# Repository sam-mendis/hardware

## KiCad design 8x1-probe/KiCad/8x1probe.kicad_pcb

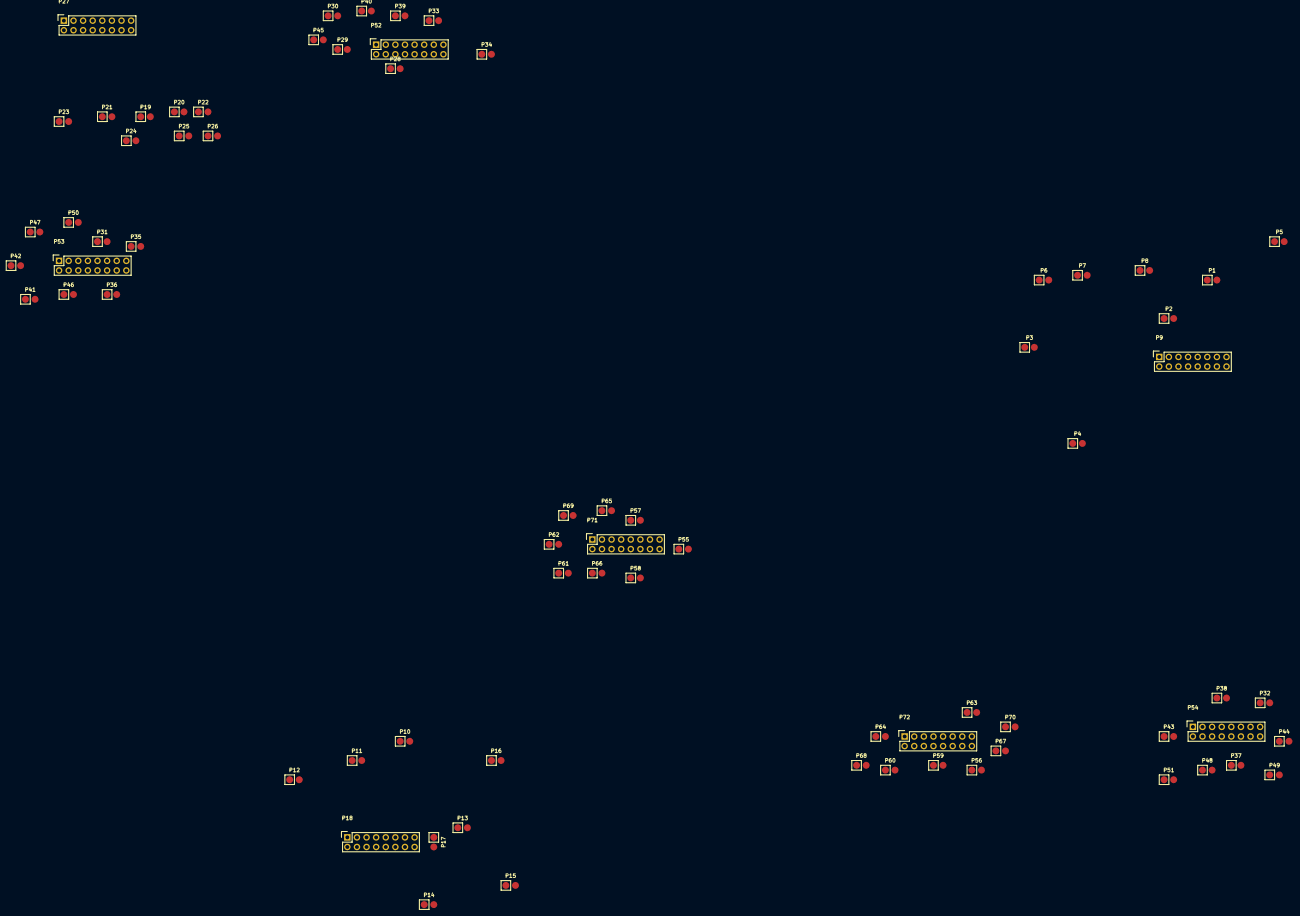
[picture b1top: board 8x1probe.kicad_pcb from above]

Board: 2 copper layers, 72 parts (0 on the bottom side), 128 nets, no tracks yet.

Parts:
P1, P2, P3, P4, P5, P6, P7, P8, P10, P11, P12, P13, P14, P15, P16, P17, P19, P20, P21, P22, P23, P24, P25, P26, P28, P29, P30, P31, P32, P33, P34, P35, P36, P37, P38, P39, P40, P41, P42, P43, P44, P45, P46, P47, P48, P49, P50, P51, P55, P56, P57, P58, P59, P60, P61, P62, P63, P64, P65, P66, P67, P68, P69, P70: 2x1_pogo_pin
P9, P18, P27, P52, P53, P54, P71, P72: CONN_02X08; Socket_Strip_Straight_2x08

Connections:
/CONN-A1: P8.1, P9.1
/CONN-A2: P8.2, P9.2
/CONN-A3: P7.1, P9.3
/CONN-A4: P7.2, P9.4
/CONN-A5: P6.1, P9.5
/CONN-A6: P6.2, P9.6
/CONN-A7: P4.1, P9.7
/CONN-A8: P4.2, P9.8
/CONN-A9: P5.1, P9.9
/CONN-A10: P5.2, P9.10
/CONN-A11: P2.1, P9.11
/CONN-A12: P2.2, P9.12
/CONN-A13: P3.1, P9.13
/CONN-A14: P3.2, P9.14
/CONN-A15: P1.1, P9.15
/CONN-A16: P1.2, P9.16
/CONN-B1: P17.1, P18.1
/CONN-B2: P17.2, P18.2
/CONN-B3: P16.1, P18.3
/CONN-B4: P16.2, P18.4
/CONN-B5: P15.1, P18.5
/CONN-B6: P15.2, P18.6
/CONN-B7: P13.1, P18.7
/CONN-B8: P13.2, P18.8
/CONN-B9: P14.1, P18.9
/CONN-B10: P14.2, P18.10
/CONN-B11: P11.1, P18.11
/CONN-B12: P11.2, P18.12
/CONN-B13: P12.1, P18.13
/CONN-B14: P12.2, P18.14
/CONN-B15: P10.1, P18.15
/CONN-B16: P10.2, P18.16
/CONN-C1: P26.1, P27.1
/CONN-C2: P26.2, P27.2
/CONN-C3: P25.1, P27.3
/CONN-C4: P25.2, P27.4
/CONN-C5: P24.1, P27.5
/CONN-C6: P24.2, P27.6
/CONN-C7: P22.1, P27.7
/CONN-C8: P22.2, P27.8
/CONN-C9: P23.1, P27.9
/CONN-C10: P23.2, P27.10
/CONN-C11: P20.1, P27.11
/CONN-C12: P20.2, P27.12
/CONN-C13: P21.1, P27.13
/CONN-C14: P21.2, P27.14
/CONN-C15: P19.1, P27.15
/CONN-C16: P19.2, P27.16
/CONN-D1: P50.1, P53.1
/CONN-D2: P50.2, P53.2
/CONN-D3: P47.1, P53.3
/CONN-D4: P47.2, P53.4
/CONN-D5: P46.1, P53.5
/CONN-D6: P46.2, P53.6
/CONN-D7: P41.1, P53.7
/CONN-D8: P41.2, P53.8
/CONN-D9: P42.1, P53.9
/CONN-D10: P42.2, P53.10
/CONN-D11: P35.1, P53.11
/CONN-D12: P35.2, P53.12
/CONN-D13: P36.1, P53.13
/CONN-D14: P36.2, P53.14
/CONN-D15: P31.1, P53.15
/CONN-D16: P31.2, P53.16
/CONN-E1: P51.1, P54.1
/CONN-E2: P51.2, P54.2
/CONN-E3: P49.1, P54.3
/CONN-E4: P49.2, P54.4
/CONN-E5: P48.1, P54.5
/CONN-E6: P48.2, P54.6
/CONN-E7: P43.1, P54.7
/CONN-E8: P43.2, P54.8
/CONN-E9: P44.1, P54.9
/CONN-E10: P44.2, P54.10
/CONN-E11: P37.1, P54.11
/CONN-E12: P37.2, P54.12
/CONN-E13: P38.1, P54.13
/CONN-E14: P38.2, P54.14
/CONN-E15: P32.1, P54.15
/CONN-E16: P32.2, P54.16
/CONN-F1: P45.1, P52.1
/CONN-F2: P45.2, P52.2
/CONN-F3: P40.1, P52.3
/CONN-F4: P40.2, P52.4
/CONN-F5: P39.1, P52.5
/CONN-F6: P39.2, P52.6
/CONN-F7: P33.1, P52.7
/CONN-F8: P33.2, P52.8
/CONN-F9: P34.1, P52.9
/CONN-F10: P34.2, P52.10
/CONN-F11: P29.1, P52.11
/CONN-F12: P29.2, P52.12
/CONN-F13: P30.1, P52.13
/CONN-F14: P30.2, P52.14
/CONN-F15: P28.1, P52.15
/CONN-F16: P28.2, P52.16
/CONN-G1: P69.1, P71.1
/CONN-G2: P69.2, P71.2
/CONN-G3: P66.1, P71.3
/CONN-G4: P66.2, P71.4
/CONN-G5: P65.1, P71.5
/CONN-G6: P65.2, P71.6
/CONN-G7: P61.1, P71.7
/CONN-G8: P61.2, P71.8
/CONN-G9: P62.1, P71.9
/CONN-G10: P62.2, P71.10
/CONN-G11: P57.1, P71.11
/CONN-G12: P57.2, P71.12
/CONN-G13: P58.1, P71.13
/CONN-G14: P58.2, P71.14
/CONN-G15: P55.1, P71.15
/CONN-G16: P55.2, P71.16
/CONN-H1: P70.1, P72.1
/CONN-H2: P70.2, P72.2
/CONN-H3: P68.1, P72.3
/CONN-H4: P68.2, P72.4
/CONN-H5: P67.1, P72.5
/CONN-H6: P67.2, P72.6
/CONN-H7: P63.1, P72.7
/CONN-H8: P63.2, P72.8
/CONN-H9: P64.1, P72.9
/CONN-H10: P64.2, P72.10
/CONN-H11: P59.1, P72.11
/CONN-H12: P59.2, P72.12
/CONN-H13: P60.1, P72.13
/CONN-H14: P60.2, P72.14
/CONN-H15: P56.1, P72.15
/CONN-H16: P56.2, P72.16

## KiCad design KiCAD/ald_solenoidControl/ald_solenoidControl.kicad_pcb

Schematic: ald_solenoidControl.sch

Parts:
C1: 0.1uF; C_0603_HandSoldering
J1, J4: Conn_01x14; Pin_Header_Straight_1x14_Pitch2.54mm
J2, J3: Conn_02x06_Odd_Even; Socket_Strip_Straight_2x06_Pitch2.54mm
JP1, JP6: Jumper_NC_Small; GS2
JP2, JP3, JP4, JP5: Jumper_NC_Dual; GS3
L1: GREY@CHRISTOFORO.NET; logo
R1: R; R_1206
R2: 500K; R_0805_HandSoldering
RN1, RN2, RN3, RN4: R_Pack04; DIP-8_SMD
U1, U2, U3, U4, U5, U6, U7, U8, U9, U10, U11, U12, U13, U14, U15, U16, U17, U18, U19, U20, U21: ASSR-1611; DIP-6_W7.62mm
U22: MCP23S17; DIP-28_W7.62mm

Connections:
+3V3: J1.2, J4.2
+5V: C1.1, J1.1, J4.1, JP2.1, JP3.1, JP4.1, JP5.1, U21.6, U22.9, U22.18
/BOT: U10.1, U20.1, U22.22
/I1: J3.2, U12.6
/I2: J2.1, U13.6
/I3: J3.6, U14.6
/I4: J2.5, U15.6
/I5: J3.10, U16.6
/I6: J2.9, U17.6
/I7: J3.11, U18.6
/I8: J2.12, U19.6
/IB: J3.7, U20.6
/IT: J2.8, U11.6
/P1: U2.1, U12.1, U22.1
/P2: U3.1, U13.1, U22.2
/P3: U4.1, U14.1, U22.3
/P4: U5.1, U15.1, U22.4
/P5: U6.1, U16.1, U22.5
/P6: U7.1, U17.1, U22.6
/P7: U8.1, U18.1, U22.7
/P8: U9.1, U19.1, U22.8
/PRE_GND: R1.2, U1.2, U2.2, U3.2, U4.2, U5.2, U6.2, U7.2, U8.2, U9.2, U10.2, U11.2, U12.2, U13.2, U14.2, U15.2, U16.2, U17.2, U18.2, U19.2, U20.2, U21.2
/TOP: U1.1, U11.1, U22.21
/V1: J3.4, U2.6
/V2: J2.3, U3.6
/V3: J3.8, U4.6
/V4: J2.7, U5.6
/V5: J3.12, U6.6
/V6: J2.11, U7.6
/V7: J3.9, U8.6
/V8: J2.10, U9.6
/VB: J3.5, U10.6
/VT: J2.6, U1.6
/V_D_EN: U21.1, U22.23
A0: JP2.2, U22.15
A1: JP3.2, U22.16
A2: JP4.2, U22.17
GND: C1.2, J1.10, J2.4, J3.1, J3.3, J4.10, JP2.3, JP3.3, JP4.3, JP5.3, R1.1, U22.10
I+: J1.11, J4.11, U12.4, U13.4, U14.4, U15.4, U16.4, U17.4, U18.4, U19.4
I-: J1.14, J4.14, U11.4, U20.4
MISO: J1.7, J4.7, U22.14
MOSI: J1.8, J4.8, U22.13
unnamed: J1.6, JP1.2
unnamed: J4.6, JP6.1
unnamed: R2.1, U21.5
SCK: J1.9, J4.9, U22.12
SCL: J1.5, J4.5
SDA: J1.4, J4.4
V+: J1.12, J4.12, U2.4, U3.4, U4.4, U5.4, U6.4, U7.4, U8.4, U9.4
V-: J1.13, J4.13, U1.4, U10.4
V_D: J1.3, J2.2, J4.3, R2.2
~CS: JP1.1, JP5.2, JP6.2, U22.11

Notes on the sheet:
ADDRESS SELECTION
POWER FLAGS
BOARD TYPE DETECTION
CONNECTORS TO SPRING PIN BOARD
RIGHT SIDE BUS CONNECTIONS
LEFT SIDE BUS CONNECTIONS

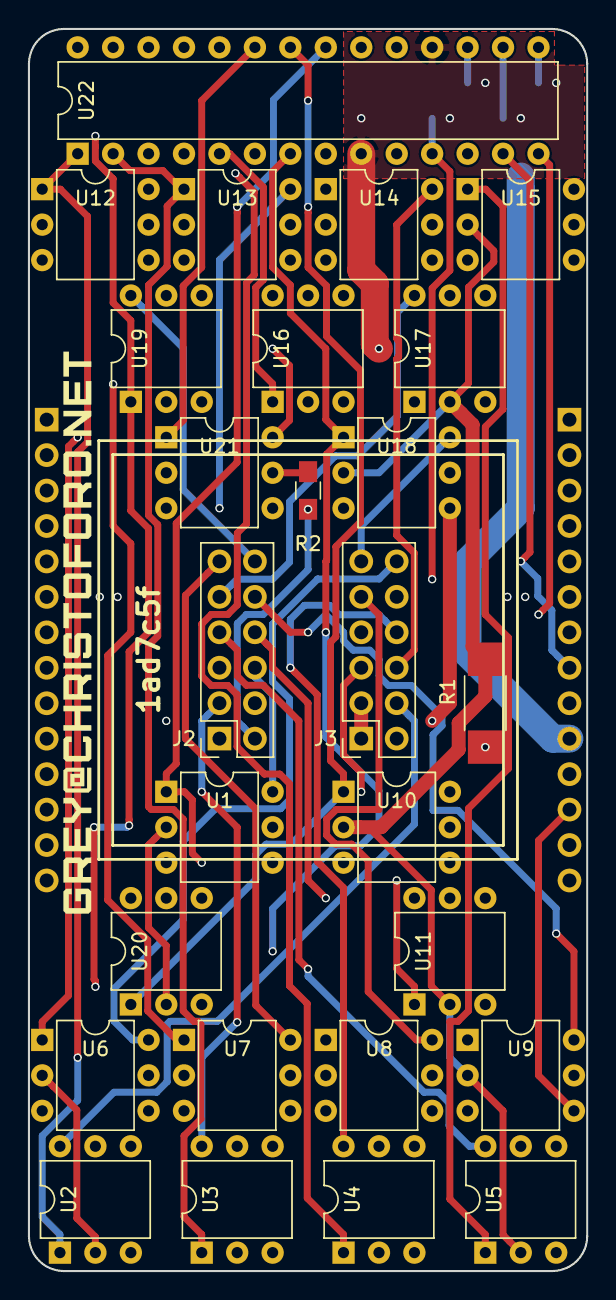
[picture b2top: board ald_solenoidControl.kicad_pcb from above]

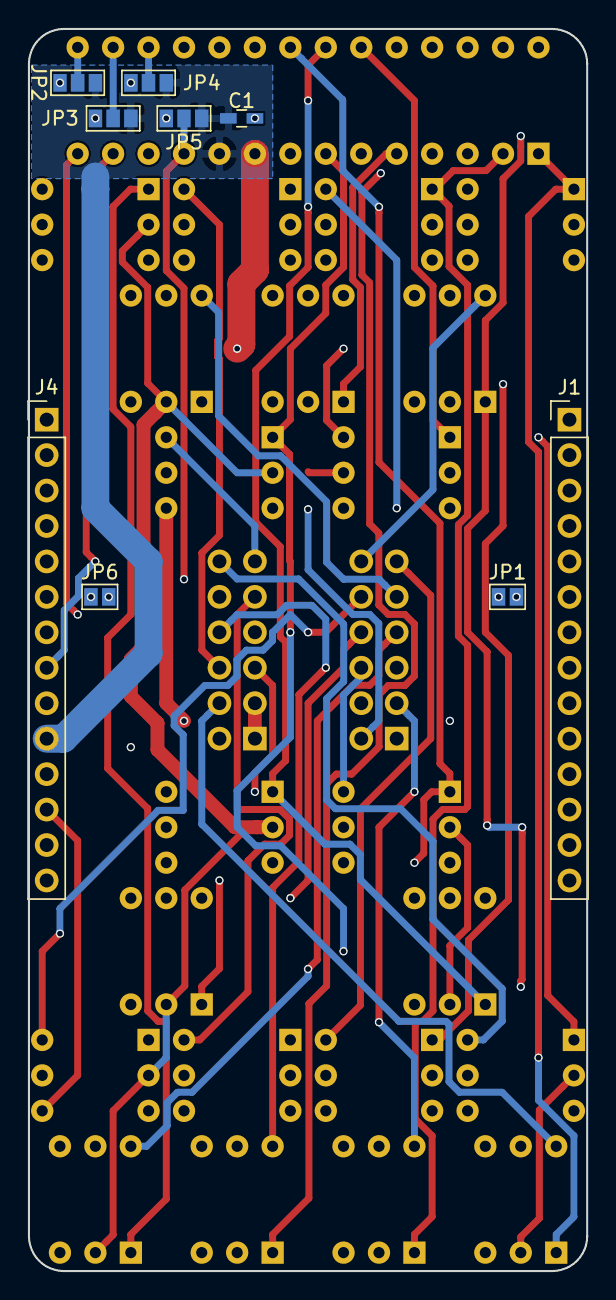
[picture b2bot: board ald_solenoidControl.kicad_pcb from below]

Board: 4 copper layers, 40.0 x 89.0 mm, 36 parts (9 on the bottom side), 52 nets.

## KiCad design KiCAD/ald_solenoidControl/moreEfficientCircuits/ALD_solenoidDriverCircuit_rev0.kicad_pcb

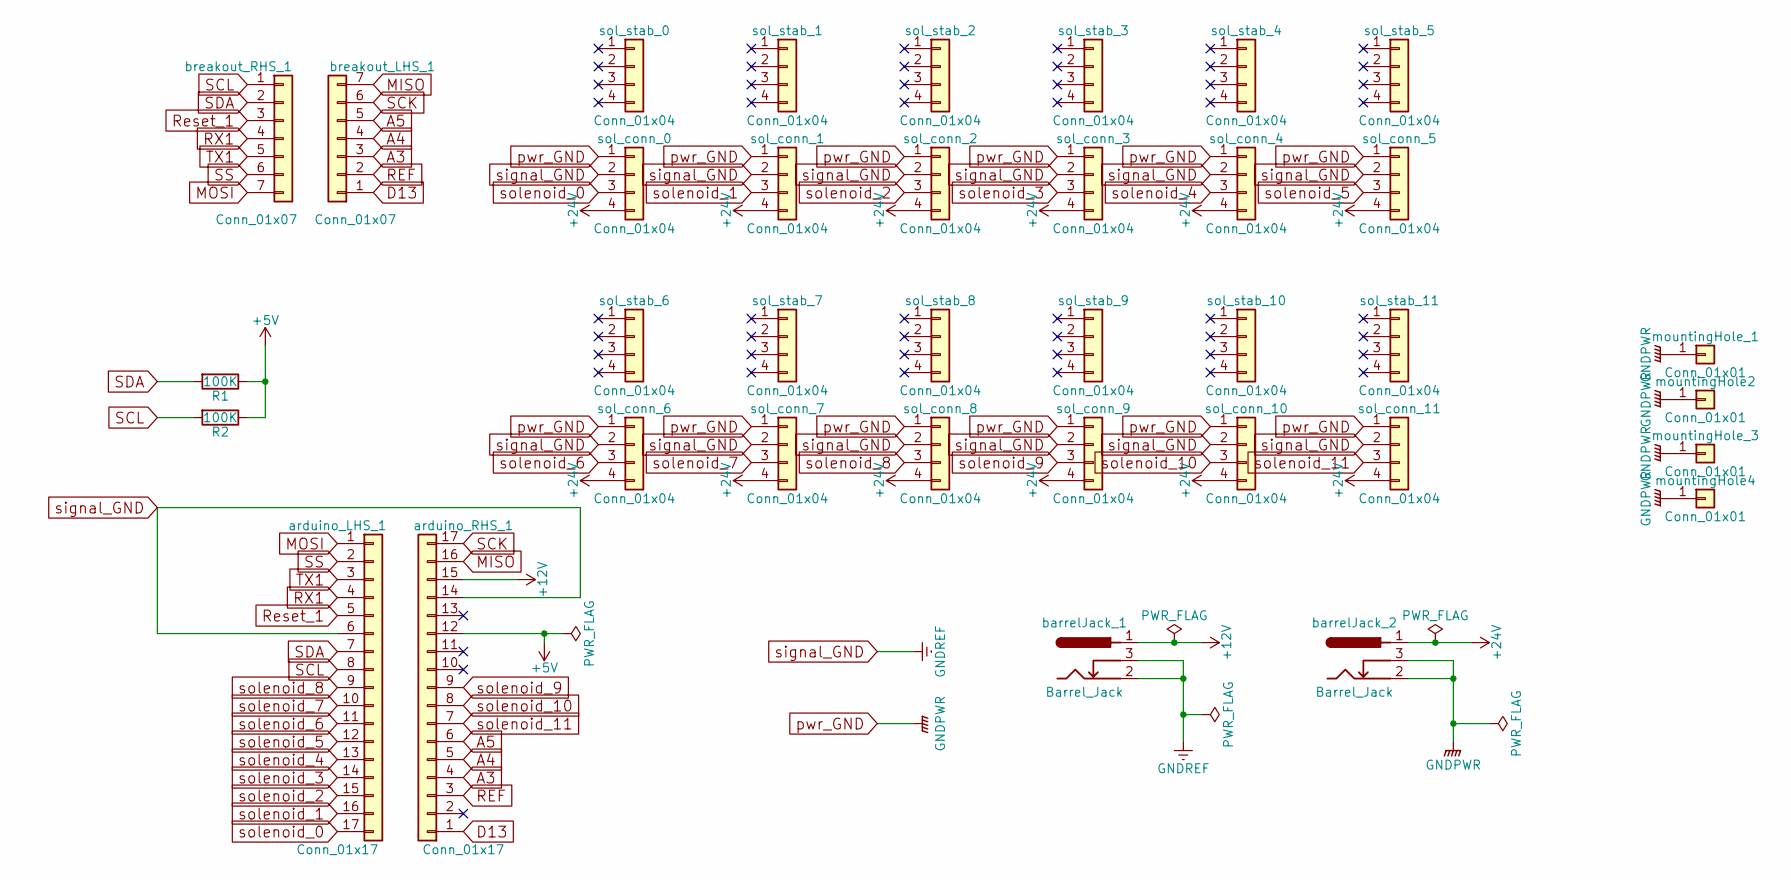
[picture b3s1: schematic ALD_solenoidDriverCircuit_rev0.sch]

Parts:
R1, R2: 100K; R_2010_HandSoldering
arduino_LHS_1: Conn_01x17; Pin_Header_Straight_1x17_Pitch2.54mm
arduino_RHS_1: Conn_01x17; Pin_Header_Straight_1x17_Pitch2.54mm
barrelJack_1, barrelJack_2: Barrel_Jack; BARREL_JACK
breakout_LHS_1: Conn_01x07; Pin_Header_Straight_1x07_Pitch2.54mm
breakout_RHS_1: Conn_01x07; Pin_Header_Straight_1x07_Pitch2.54mm
mountingHole2, mountingHole4: Conn_01x01; MountingHole_3mm_Pad
mountingHole_1, mountingHole_3: Conn_01x01; MountingHole_3mm_Pad
sol_conn_0, sol_conn_1, sol_conn_2, sol_conn_3, sol_conn_4, sol_conn_5, sol_conn_6, sol_conn_7, sol_conn_8, sol_conn_9, sol_conn_10, sol_conn_11: Conn_01x04; Pin_Header_Straight_1x04_Pitch2.54mm
sol_stab_0, sol_stab_1, sol_stab_2, sol_stab_3, sol_stab_4, sol_stab_5, sol_stab_6, sol_stab_7, sol_stab_8, sol_stab_9, sol_stab_10, sol_stab_11: Conn_01x04; Pin_Header_Straight_1x04_Pitch2.54mm

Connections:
+5V: R1.1, R2.1, arduino_RHS_1.12
+12V: arduino_RHS_1.15, barrelJack_1.1
+24V: barrelJack_2.1, sol_conn_0.4, sol_conn_1.4, sol_conn_2.4, sol_conn_3.4, sol_conn_4.4, sol_conn_5.4, sol_conn_6.4, sol_conn_7.4, sol_conn_8.4, sol_conn_9.4, sol_conn_10.4, sol_conn_11.4
A3: arduino_RHS_1.4, breakout_LHS_1.3
A4: arduino_RHS_1.5, breakout_LHS_1.4
A5: arduino_RHS_1.6, breakout_LHS_1.5
D13: arduino_RHS_1.1, breakout_LHS_1.1
MISO: arduino_RHS_1.16, breakout_LHS_1.7
MOSI: arduino_LHS_1.1, breakout_RHS_1.7
REF: arduino_RHS_1.3, breakout_LHS_1.2
RX1: arduino_LHS_1.4, breakout_RHS_1.4
Reset_1: arduino_LHS_1.5, breakout_RHS_1.3
SCK: arduino_RHS_1.17, breakout_LHS_1.6
SCL: R2.2, arduino_LHS_1.8, breakout_RHS_1.1
SDA: R1.2, arduino_LHS_1.7, breakout_RHS_1.2
SS: arduino_LHS_1.2, breakout_RHS_1.6
TX1: arduino_LHS_1.3, breakout_RHS_1.5
pwr_GND: barrelJack_2.2, barrelJack_2.3, mountingHole2.1, mountingHole4.1, mountingHole_1.1, mountingHole_3.1, sol_conn_0.1, sol_conn_1.1, sol_conn_2.1, sol_conn_3.1, sol_conn_4.1, sol_conn_5.1, sol_conn_6.1, sol_conn_7.1, sol_conn_8.1, sol_conn_9.1, sol_conn_10.1, sol_conn_11.1
signal_GND: arduino_LHS_1.6, arduino_RHS_1.14, barrelJack_1.2, barrelJack_1.3, sol_conn_0.2, sol_conn_1.2, sol_conn_2.2, sol_conn_3.2, sol_conn_4.2, sol_conn_5.2, sol_conn_6.2, sol_conn_7.2, sol_conn_8.2, sol_conn_9.2, sol_conn_10.2, sol_conn_11.2
solenoid_0: arduino_LHS_1.17, sol_conn_0.3
solenoid_1: arduino_LHS_1.16, sol_conn_1.3
solenoid_2: arduino_LHS_1.15, sol_conn_2.3
solenoid_3: arduino_LHS_1.14, sol_conn_3.3
solenoid_4: arduino_LHS_1.13, sol_conn_4.3
solenoid_5: arduino_LHS_1.12, sol_conn_5.3
solenoid_6: arduino_LHS_1.11, sol_conn_6.3
solenoid_7: arduino_LHS_1.10, sol_conn_7.3
solenoid_8: arduino_LHS_1.9, sol_conn_8.3
solenoid_9: arduino_RHS_1.9, sol_conn_9.3
solenoid_10: arduino_RHS_1.8, sol_conn_10.3
solenoid_11: arduino_RHS_1.7, sol_conn_11.3

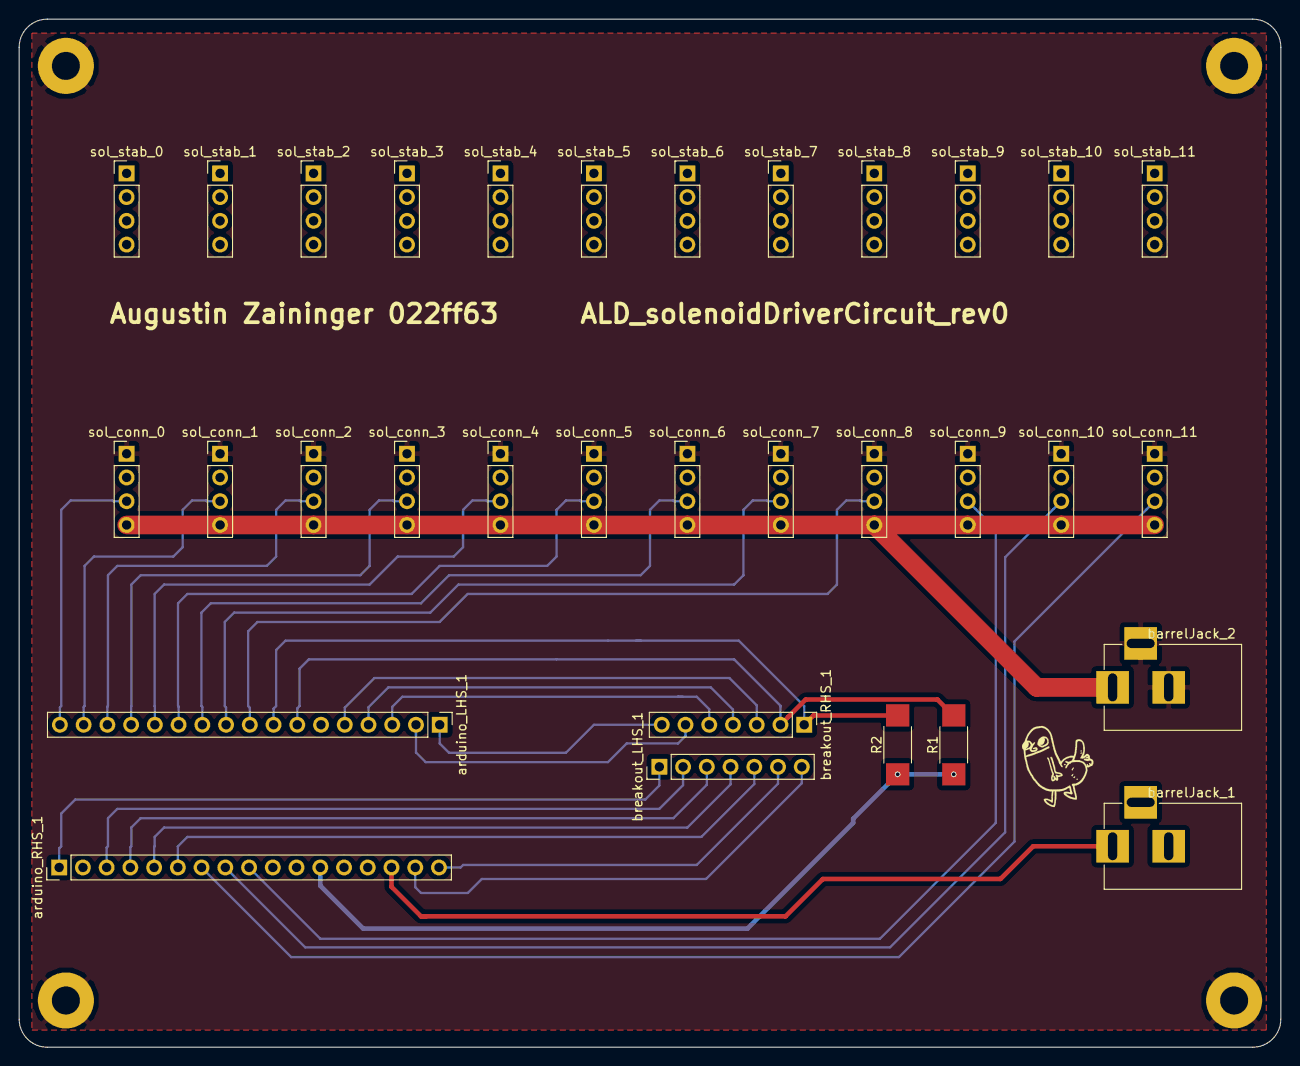
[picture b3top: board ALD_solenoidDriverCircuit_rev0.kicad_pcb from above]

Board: 2 copper layers, 135.0 x 110.0 mm, 36 parts (0 on the bottom side), 31 nets.

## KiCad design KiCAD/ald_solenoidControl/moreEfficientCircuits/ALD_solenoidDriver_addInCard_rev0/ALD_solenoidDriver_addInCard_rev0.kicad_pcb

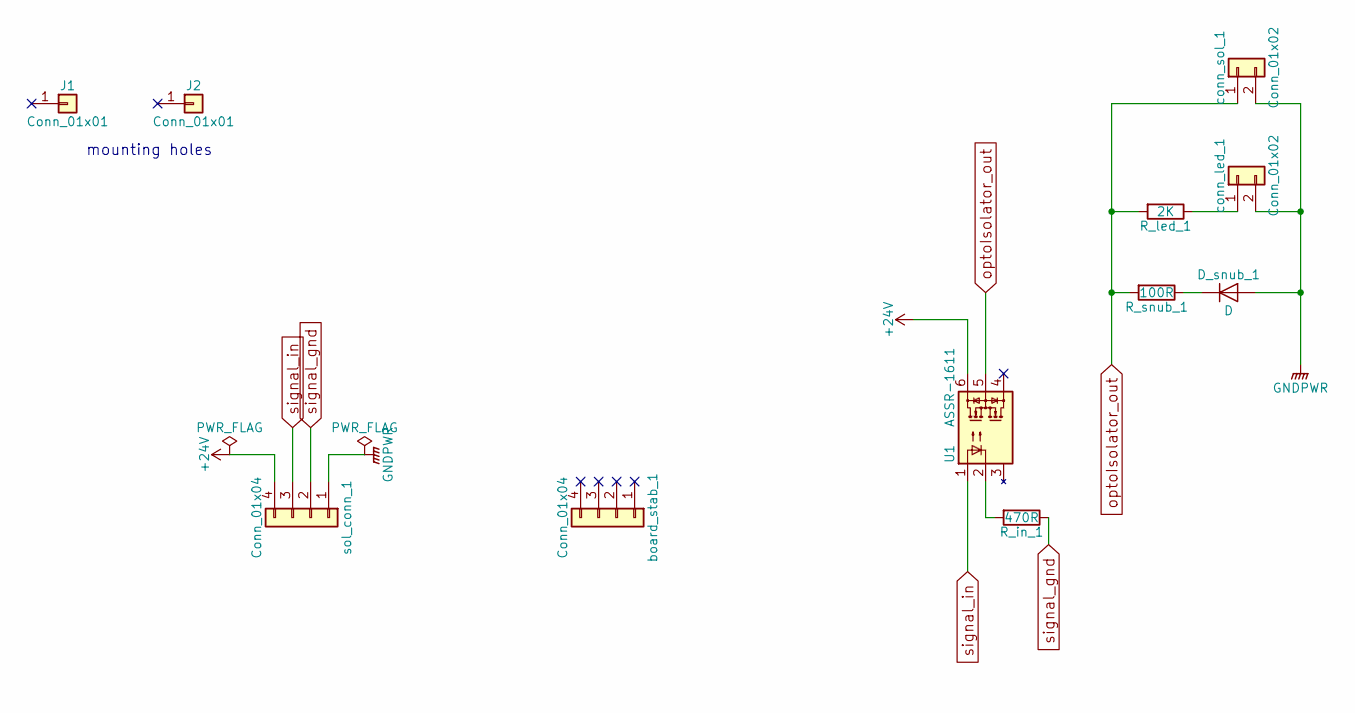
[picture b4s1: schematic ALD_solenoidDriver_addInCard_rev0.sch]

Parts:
D_snub_1: D; D_A-405_P7.62mm_Horizontal; farnellCode 1695714
J1, J2: Conn_01x01; MountingHole_3mm_Pad
R_in_1: 470R; R_2010_HandSoldering
R_led_1: 2K; R_2010_HandSoldering
R_snub_1: 100R; R_2010_HandSoldering
U1: ASSR-1611; DIP-6_W7.62mm
board_stab_1: Conn_01x04; Pin_Header_Angled_1x04_Pitch2.54mm
conn_led_1: Conn_01x02; Pin_Header_Angled_1x02_Pitch2.54mm
conn_sol_1: Conn_01x02; Pin_Header_Angled_1x02_Pitch2.54mm
sol_conn_1: Conn_01x04; Pin_Header_Angled_1x04_Pitch2.54mm

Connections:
+24V: U1.6, sol_conn_1.4
GNDPWR: D_snub_1.2 (A), conn_led_1.2, conn_sol_1.2, sol_conn_1.1
unnamed: D_snub_1.1 (K), R_snub_1.1
unnamed: R_in_1.2, U1.2
unnamed: R_led_1.1, conn_led_1.1
optoIsolator_out: R_led_1.2, R_snub_1.2, U1.5, conn_sol_1.1
signal_gnd: R_in_1.1, sol_conn_1.2
signal_in: U1.1, sol_conn_1.3

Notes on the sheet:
mounting holes

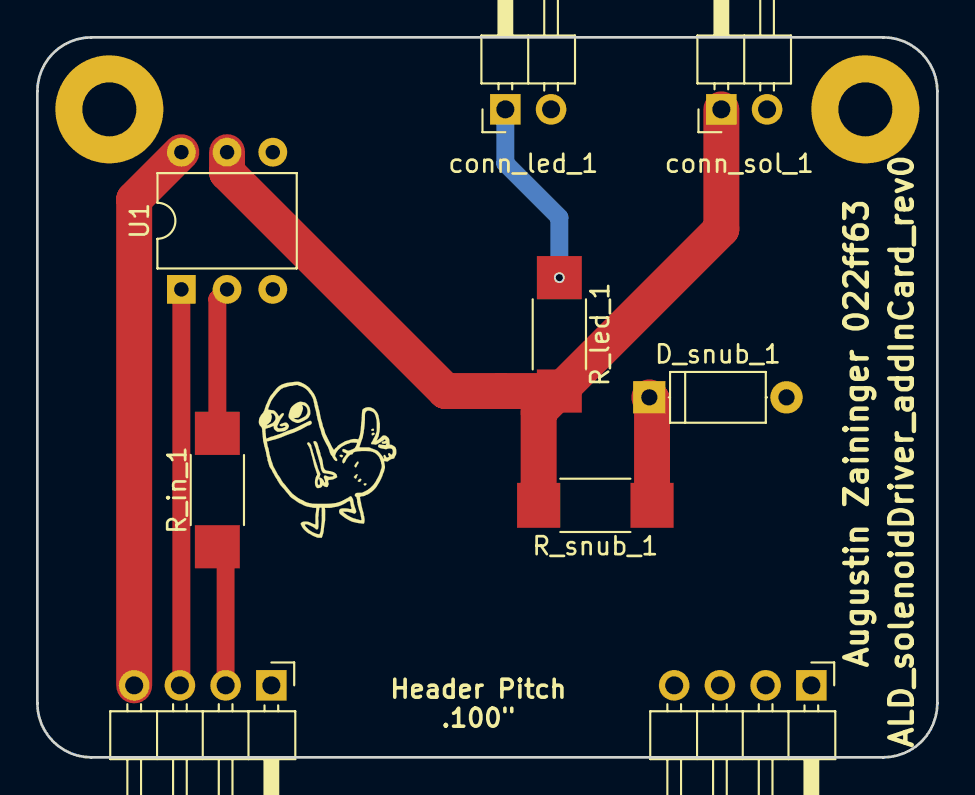
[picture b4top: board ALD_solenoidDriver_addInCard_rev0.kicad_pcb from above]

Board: 2 copper layers, 50.0 x 40.0 mm, 11 parts (0 on the bottom side), 8 nets.

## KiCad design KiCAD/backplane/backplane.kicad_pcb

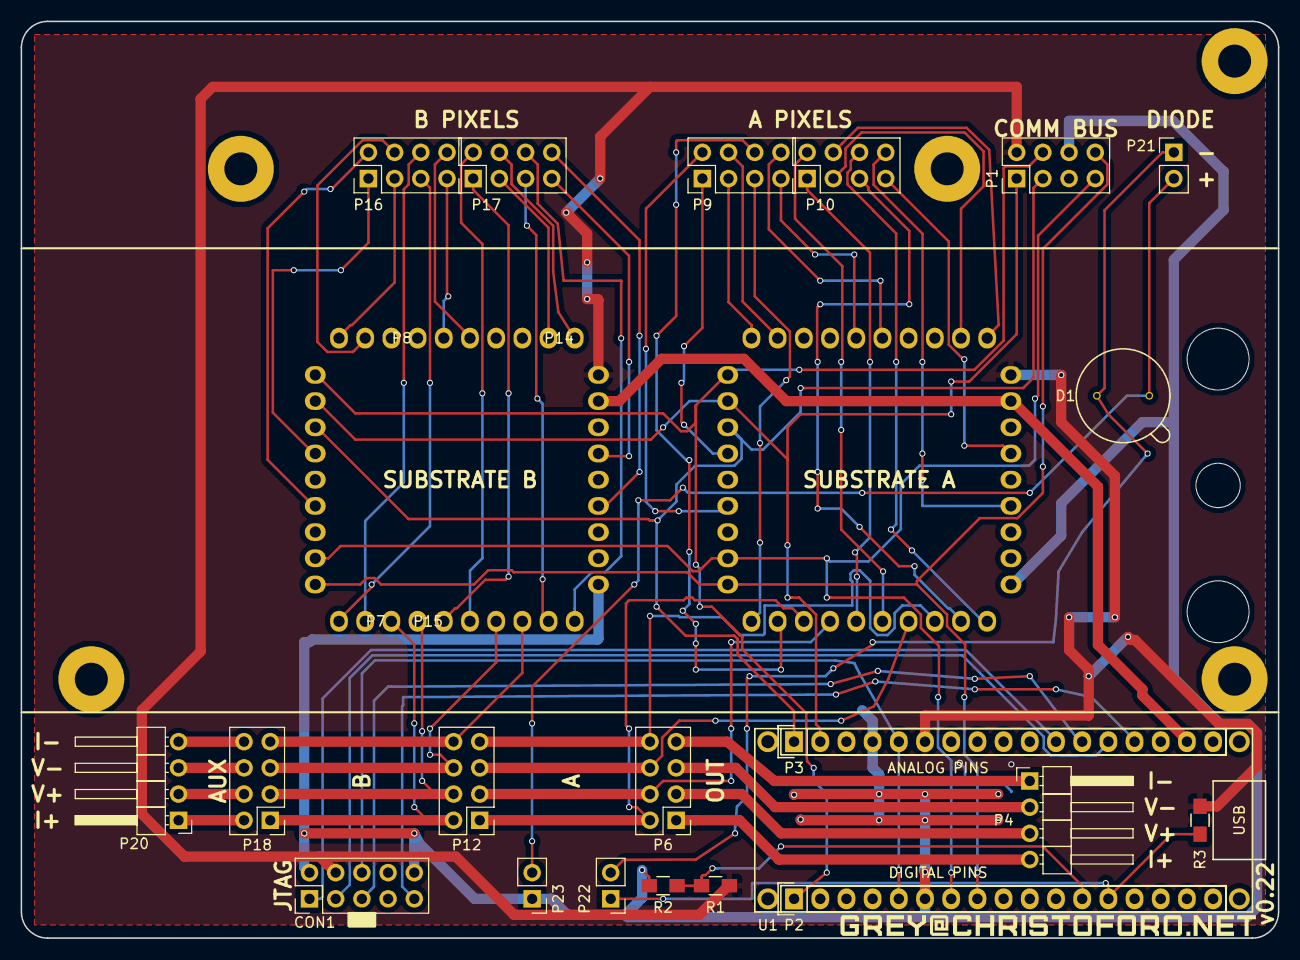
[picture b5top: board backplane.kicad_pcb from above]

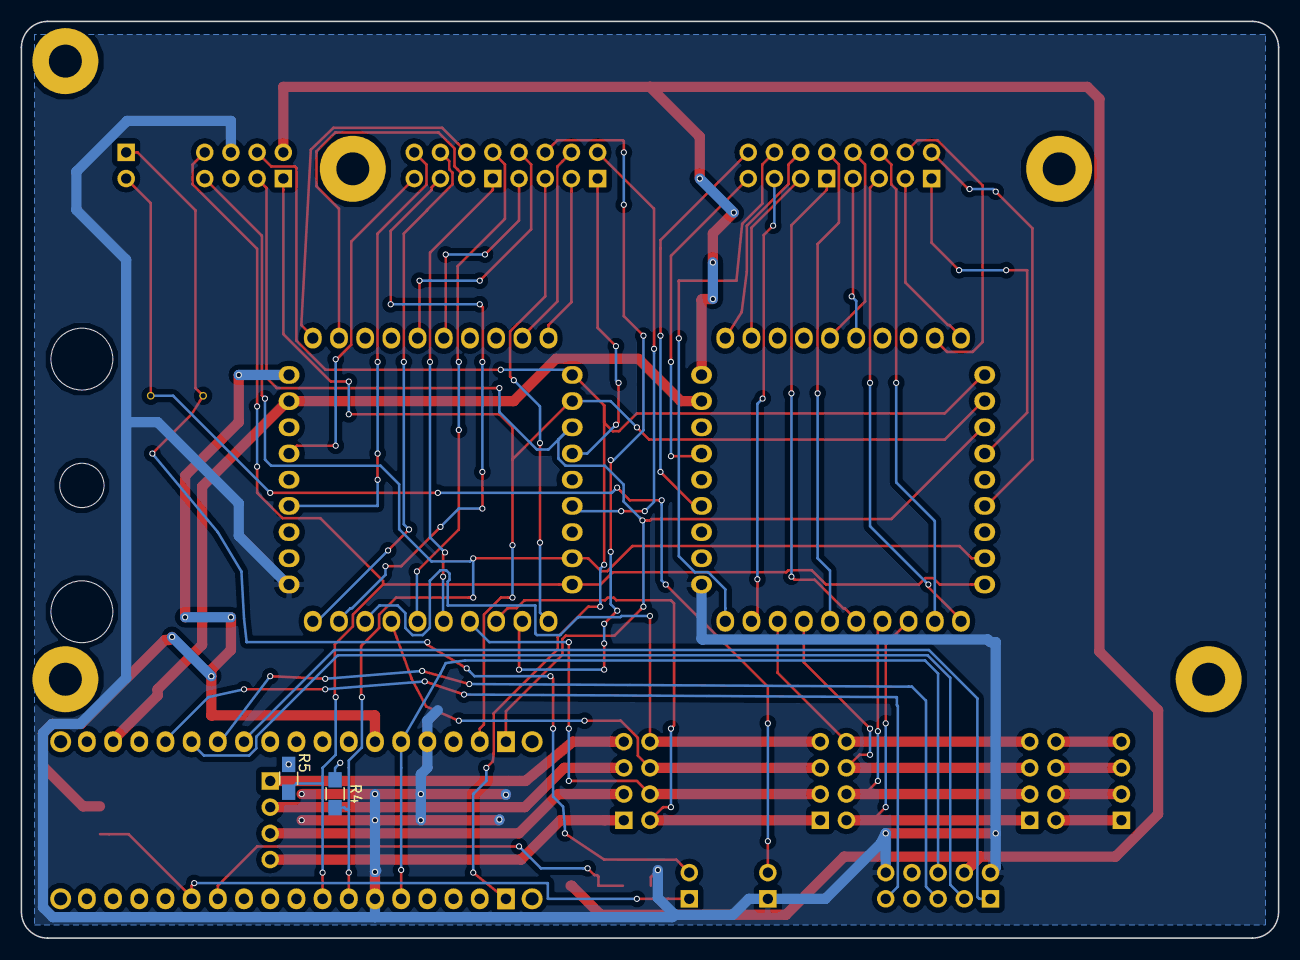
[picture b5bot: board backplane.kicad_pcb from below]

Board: 2 copper layers, 121.9 x 88.9 mm, 107 parts (2 on the bottom side), 65 nets.

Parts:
CON1: AVR-JTAG-10; Pin_Header_Straight_2x05_Pitch2.54mm
D1: BPW21; TO-5_2-PIN
P1, P6, P9, P10, P12, P16, P17, P18: CONN_02X04; Pin_Header_Straight_2x04_Pitch2.54mm
P2, P3: CONN_01X17; Socket_Strip_Straight_1x17
P4, P20: CONN_01X04; Pin_Header_Angled_1x04_Pitch2.54mm
P5, P7, P8, P11, P13, P14, P15, P19, P24, P25, P26, P27, P28, P29, P30, P31, P32, P33, P34, P35, P36, P37, P38, P39, P40, P41, P42, P43, P44, P45, P46, P47, P48, P49, P50, P51, P52, P53, P54, P55, P56, P57, P58, P59, P60, P61, P62, P63, P64, P65, P66, P67, P68, P69, P70, P71, P72, P73, P74, P75, P76, P77, P78, P79, P80, P81, P82, P83, P84, P85, P86, P87, P88, P89, P90, P91: CONN_01X01; 4994-0-15-15-11-27-10-0
P21, P22, P23: CONN_01X02; Pin_Header_Straight_1x02_Pitch2.54mm
P92, P96, P97, P98, P99: CONN_01X01; MountingHole_3.2mm_M3_Pad
P93, P95: CONN_01X01; MountingHole_6mm
P94: CONN_01X01; MountingHole_4.3mm_M4
R1: 70K; R_0805_HandSoldering
R2: 30K; R_0805_HandSoldering
R3: 2k; R_0805_HandSoldering
R4, R5: 10K; R_0805_HandSoldering
U1: ARDUINO_MICRO; arduino_micro

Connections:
+3V3: P3.16, P33.1, P51.1
+5V: CON1.4, P1.2, P3.6, P13.1, P50.1, R1.1, R3.1, R4.1, R5.1
/ANODE: D1.2, P21.2, P23.2
/CATHODE: D1.1, P21.1, P22.2
A0_I: P9.3, P72.1
A0_V: P9.4, P74.1
A1_I: P9.5, P73.1
A1_V: P9.6, P75.1
A2_I: P9.7, P80.1
A2_V: P9.8, P82.1
A3_I: P10.1, P81.1
A3_V: P10.2, P83.1
A4_I: P10.3, P88.1
A4_V: P10.4, P90.1
A5_I: P10.5, P89.1
A5_V: P10.6, P91.1
ADC11: P2.13, P22.1, R3.2
AIN0: P2.12, R1.2, R2.1
AL_I: P9.1, P44.1
AL_V: P9.2, P46.1
AR_I: P10.7, P53.1
AR_V: P10.8, P55.1
AUX_OUT_I+: P18.2, P20.1
AUX_OUT_I-: P18.8, P20.4
AUX_OUT_V+: P18.4, P20.2
AUX_OUT_V-: P18.6, P20.3
A_I+: P6.2, P12.1, P77.1
A_I-: P6.8, P12.7, P87.1
A_V+: P6.4, P12.3, P79.1
A_V-: P6.6, P12.5, P85.1
B0_I: P5.1, P16.3
B0_V: P8.1, P16.4
B1_I: P7.1, P16.5
B1_V: P11.1, P16.6
B2_I: P16.7, P60.1
B2_V: P16.8, P62.1
B3_I: P17.1, P61.1
B3_V: P17.2, P63.1
B4_I: P17.3, P68.1
B4_V: P17.4, P70.1
B5_I: P17.5, P69.1
B5_V: P17.6, P71.1
BL_I: P16.1, P27.1
BL_V: P16.2, P29.1
BR_I: P17.7, P35.1
BR_V: P17.8, P37.1
B_I+: P12.2, P15.1, P18.1
B_I-: P12.8, P18.7, P67.1
B_V+: P12.4, P18.3, P59.1
B_V-: P12.6, P18.5, P65.1
GND: CON1.2, CON1.10, P1.6, P2.6, P3.4, P23.1, P40.1, P58.1, R2.2
MISO: P1.1, P3.2, P25.1, P42.1
MOSI: P1.4, P2.1, P24.1, P41.1
OUT_I+: P4.4, P6.1
OUT_I-: P4.1, P6.7
OUT_V+: P4.3, P6.3
OUT_V-: P4.2, P6.5
RESET: CON1.6, P2.5, P3.5
SCK: P1.3, P3.1, P26.1, P43.1
SCL: P1.8, P2.8, P32.1, P49.1, R5.2
SDA: P1.7, P2.7, P31.1, P48.1, R4.2
TCK: CON1.1, P3.11
TDI: CON1.9, P3.14
TDO: CON1.3, P3.13
TMS: CON1.5, P3.12

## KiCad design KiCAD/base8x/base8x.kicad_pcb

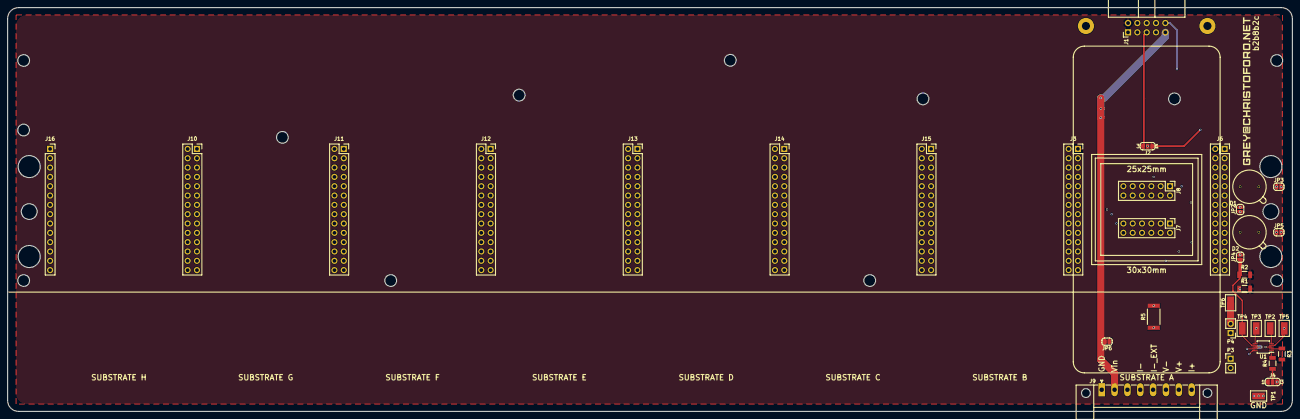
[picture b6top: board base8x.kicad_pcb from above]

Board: 4 copper layers, 350.0 x 110.0 mm, 58 parts (1 on the bottom side), 28 nets.

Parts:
C1: 1uF; C_1206_3216Metric
D1, D2: BPW21
J1: Conn_02x05_Odd_Even; IDC-Header_2x05_P2.54mm_Horizontal
J2, J4: GS3; SolderJumper-3_P1.3mm_Open_RoundedPad1.0x1.5mm_NumberLabels
J3, J6, J10, J11, J12, J13, J14, J15: Conn_02x14_Counter_Clockwise; PinSocket_2x14_P2.54mm_Vertical
J7, J8: Conn_02x06_Counter_Clockwise; PinHeader_2x06_P2.54mm_Vertical
J9: Screw_Terminal_01x08; PhoenixContact_MC_1,5_8-GF-3.5_1x08_P3.50mm_Horizontal_Thre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
J16: Conn_01x14; PinSocket_1x14_P2.54mm_Vertical
JP2, JP3, JP4, JP5, JP6: Jumper_NO_Small; SolderJumper-2_P1.3mm_Open_RoundedPad1.0x1.5mm
L1: GREY@CHRISTOFORO.NET; logo
MK1, MK2: Mounting_Hole_PAD; MountingHole_2.2mm_M2_Pad
MK3, MK4, MK9, MK11: Mounting_Hole; MountingHole_6mm
MK5, MK7, MK8, MK12, MK13, MK14, MK15, MK16, MK17, MK18, MK19, MK20: Mounting_Hole; MountingHole_3.2mm_M3
MK6, MK10: Mounting_Hole; MountingHole_4.3mm_M4
P3, P4: CONN_01X02; PinHeader_1x02_P2.54mm_Vertical
R1, R2: 1.2K; R_1206_3216Metric
R3, R4: 10K; R_1206_3216Metric
R5: 1; R_2512_6332Metric
TP1, TP2, TP3, TP4, TP5, TP6: Test_Point; Test_Point_S1751-46R
U1: ADS1115; MSOP-10_3x3mm_P0.5mm

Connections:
+3V3: J3.3, J6.4
+5V: C1.1, J1.2, J3.1, J4.1, J6.2, JP6.1, R1.2, R2.2, R3.2, U1.8
/Vin: J1.9, J9.2, JP6.2
A_I+: J3.21, J6.22, J9.8
A_I-: J3.27, J6.28, J9.4, P4.2, R5.2, TP6.1
A_I-_EXT: J9.5, P3.1, P4.1, R5.1
A_V+: J3.23, J6.24, J9.7
A_V-: J3.25, J6.26, J9.6
A_V_D: J2.2, J3.5, J6.6
A_V_D_EXT: J1.5, J2.3
A_V_D_LOC: J2.1, TP5.1, U1.4
GND: C1.2, J1.6, J3.19, J3.20, J4.3, J6.20, J9.1, J10.19, J10.20, J11.19, J11.20, J12.19, J12.20, J13.19, J13.20, J14.19, J14.20, J15.19, J15.20, J16.10, JP3.2, JP5.2, MK1.1, MK2.1, P3.2, TP1.1, U1.3
MISO: J1.1, J3.13, J6.14
MOSI: J1.4, J3.15, J6.16
unnamed: D1.1, JP2.2
unnamed: D1.2, JP3.1
unnamed: D2.1, JP4.2
unnamed: D2.2, JP5.1
unnamed: J4.2, R4.1
unnamed: JP2.1, R1.1, TP3.1, U1.6
unnamed: JP4.1, R2.1, TP4.1, U1.7
unnamed: R3.1, U1.2
unnamed: R4.2, U1.1
unnamed: TP2.1, U1.5
SCK: J1.3, J3.17, J6.18
SCL: J1.8, J3.9, J6.10, U1.10
SDA: J1.7, J3.7, J6.8, U1.9
~A_CS: J1.10, J3.11, J6.12
